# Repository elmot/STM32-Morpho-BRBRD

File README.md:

# STM32-Morpho-BRBRD

Prototyping shield for any STM32 Nucleo64 board.

### Features:

* 55x70 mm
* All MCU pins solderable
* Wide DIL-28 footprint
* Narrow DIL-28 footprint
* (T)SSOP-28 (pitch 0.65mm) footprint (bottom)
* SOP-28 (pitch 1.27mm) footprint (top)
* Four SOT23-5 footprints (two per side)
* Six 1206 footprints in two chains (one chain per side)
* Free pads and pins for custom soldering

### NOTE

Original STM Morpho form-factor contains 2 * 19 connectrors. This shield uses 2 * 20 which are easier to buy. Be careful during soldering and connecting the shield to the Nucleo board.

### Status

12-Aug-18: First batch of PCBs submitted to PCB manufacturer

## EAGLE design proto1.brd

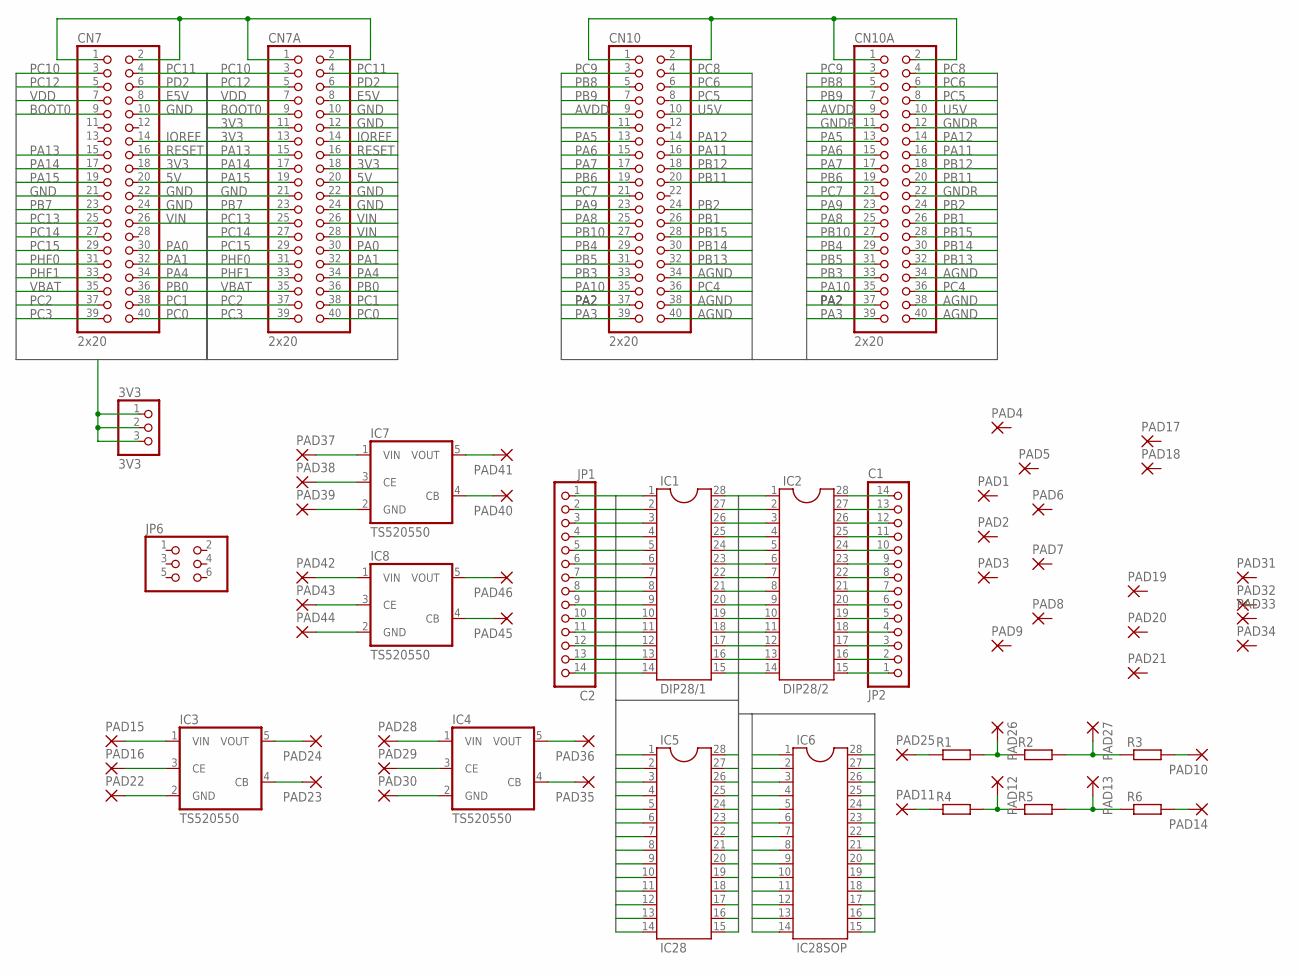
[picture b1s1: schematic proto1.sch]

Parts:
3V3: 3V3; 1X03
CN7, CN7A, CN10, CN10A: 2x20; 2X20
IC1: DIP28/1; DIL28-6
IC2: DIP28/2; DIL28-3
IC3, IC4, IC7, IC8: TS520550; SOT25
IC5: IC28; SSOP28
IC6: IC28SOP; SOP28
JP1: C2; 1X14
JP2: C1; 1X14
JP6: PINHD-2X3; 2X03
PAD1, PAD2, PAD3, PAD4, PAD5, PAD6, PAD7, PAD8, PAD9, PAD10, PAD11, PAD12, PAD13, PAD14, PAD15, PAD16, PAD17, PAD18, PAD19, PAD20, PAD21, PAD22, PAD23, PAD24, PAD25, PAD26, PAD27, PAD28, PAD29, PAD30, PAD31, PAD32, PAD33, PAD34, PAD35, PAD36, PAD37, PAD38, PAD39, PAD40, PAD41, PAD42, PAD43, PAD44, PAD45, PAD46: SMD2; SMD1,27-2,54
R1, R2, R3, R4, R5, R6: R-EU_R1206; R1206

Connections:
3V3: 3V3.1, 3V3.2, 3V3.3, CN7.18, CN7A.11, CN7A.13, CN7A.18
5V: CN7.20, CN7A.20
AGND: CN10.34, CN10.38, CN10.40, CN10A.34, CN10A.38, CN10A.40
AVDD: CN10.9, CN10A.9
BOOT0: CN7.9, CN7A.9
E5V: CN7.8, CN7A.8
GND: CN7.10, CN7.21, CN7.22, CN7.24, CN7A.10, CN7A.12, CN7A.21, CN7A.22, CN7A.24
GNDR: CN10.11, CN10A.11, CN10A.12, CN10A.22
IC1: IC1.1, IC5.1, IC6.28, JP1.1
IC2: IC1.2, IC5.2, IC6.27, JP1.2
IC3: IC1.3, IC5.3, IC6.26, JP1.3
IC4: IC1.4, IC5.4, IC6.25, JP1.4
IC5: IC1.5, IC5.5, IC6.24, JP1.5
IC6: IC1.6, IC5.6, IC6.23, JP1.6
IC7: IC1.7, IC5.7, IC6.22, JP1.7
IC8: IC1.8, IC5.8, IC6.21, JP1.8
IC9: IC1.9, IC5.9, IC6.20, JP1.9
IC10: IC1.10, IC5.10, IC6.19, JP1.10
IC11: IC1.11, IC5.11, IC6.18, JP1.11
IC12: IC1.12, IC5.12, IC6.17, JP1.12
IC13: IC1.13, IC5.13, IC6.16, JP1.13
IC14: IC1.14, IC5.14, IC6.15, JP1.14
IC15: IC1.15, IC2.14, IC5.15, IC6.14
IC16: IC1.16, IC2.13, IC5.16, IC6.13
IC17: IC1.17, IC2.12, IC5.17, IC6.12
IC18: IC1.18, IC2.11, IC5.18, IC6.11
IC19: IC1.19, IC2.10, IC5.19, IC6.10
IC20: IC1.20, IC2.9, IC5.20, IC6.9
IC21: IC1.21, IC2.8, IC5.21, IC6.8
IC22: IC1.22, IC2.7, IC5.22, IC6.7
IC23: IC1.23, IC2.6, IC5.23, IC6.6
IC24: IC1.24, IC2.5, IC5.24, IC6.5
IC25: IC1.25, IC2.4, IC5.25, IC6.4
IC26: IC1.26, IC2.3, IC5.26, IC6.3
IC27: IC1.27, IC2.2, IC5.27, IC6.2
IC28: IC1.28, IC2.1, IC5.28, IC6.1
IOREF: CN7.14, CN7A.14
unnamed: CN10.1, CN10.2, CN10A.1, CN10A.2
unnamed: CN7.1, CN7.2, CN7A.1, CN7A.2
unnamed: IC2.28, JP2.14
unnamed: IC2.27, JP2.13
unnamed: IC2.26, JP2.12
unnamed: IC2.25, JP2.11
unnamed: IC2.24, JP2.10
unnamed: IC2.23, JP2.9
unnamed: IC2.22, JP2.8
unnamed: IC2.21, JP2.7
unnamed: IC2.20, JP2.6
unnamed: IC2.19, JP2.5
unnamed: IC2.18, JP2.4
unnamed: IC2.17, JP2.3
unnamed: IC2.16, JP2.2
unnamed: IC2.15, JP2.1
unnamed: PAD25.1, R1.1
unnamed: PAD26.1, R1.2, R2.1
unnamed: PAD27.1, R2.2, R3.1
unnamed: PAD10.1, R3.2
unnamed: PAD11.1, R4.1
unnamed: PAD12.1, R4.2, R5.1
unnamed: PAD13.1, R5.2, R6.1
unnamed: PAD14.1, R6.2
unnamed: IC3.1 (VIN), PAD15.1
unnamed: IC3.3 (CE), PAD16.1
unnamed: IC3.2 (GND), PAD22.1
unnamed: IC3.4 (CB), PAD23.1
unnamed: IC3.5 (VOUT), PAD24.1
unnamed: IC4.1 (VIN), PAD28.1
unnamed: IC4.3 (CE), PAD29.1
unnamed: IC4.2 (GND), PAD30.1
unnamed: IC4.4 (CB), PAD35.1
unnamed: IC4.5 (VOUT), PAD36.1
unnamed: IC7.1 (VIN), PAD37.1
unnamed: IC7.3 (CE), PAD38.1
unnamed: IC7.2 (GND), PAD39.1
unnamed: IC7.4 (CB), PAD40.1
unnamed: IC7.5 (VOUT), PAD41.1
unnamed: IC8.1 (VIN), PAD42.1
unnamed: IC8.3 (CE), PAD43.1
unnamed: IC8.2 (GND), PAD44.1
unnamed: IC8.4 (CB), PAD45.1
unnamed: IC8.5 (VOUT), PAD46.1
PA0: CN7.30, CN7A.30
PA1: CN7.32, CN7A.32
PA2: CN10.37, CN10A.37
PA3: CN10.39, CN10A.39
PA4: CN7.34, CN7A.34
PA5: CN10.13, CN10A.13
PA6: CN10.15, CN10A.15
PA7: CN10.17, CN10A.17
PA8: CN10.25, CN10A.25
PA9: CN10.23, CN10A.23
PA10: CN10.35, CN10A.35
PA11: CN10.16, CN10A.16
PA12: CN10.14, CN10A.14
PA13: CN7.15, CN7A.15
PA14: CN7.17, CN7A.17
PA15: CN7.19, CN7A.19
PB0: CN7.36, CN7A.36
PB1: CN10.26, CN10A.26
PB2: CN10.24, CN10A.24
PB3: CN10.33, CN10A.33
PB4: CN10.29, CN10A.29
PB5: CN10.31, CN10A.31
PB6: CN10.19, CN10A.19
PB7: CN7.23, CN7A.23
PB8: CN10.5, CN10A.5
PB9: CN10.7, CN10A.7
PB10: CN10.27, CN10A.27
PB11: CN10.20, CN10A.20
PB12: CN10.18, CN10A.18
PB13: CN10.32, CN10A.32
PB14: CN10.30, CN10A.30
PB15: CN10.28, CN10A.28
PC0: CN7.40, CN7A.40
PC1: CN7.38, CN7A.38
PC2: CN7.37, CN7A.37
PC3: CN7.39, CN7A.39
PC4: CN10.36, CN10A.36
PC5: CN10.8, CN10A.8
PC6: CN10.6, CN10A.6
PC7: CN10.21, CN10A.21
PC8: CN10.4, CN10A.4
PC9: CN10.3, CN10A.3
PC10: CN7.3, CN7A.3
PC11: CN7.4, CN7A.4
PC12: CN7.5, CN7A.5
PC13: CN7.25, CN7A.25
PC14: CN7.27, CN7A.27
PC15: CN7.29, CN7A.29
PD2: CN7.6, CN7A.6
PHF0: CN7.31, CN7A.31
PHF1: CN7.33, CN7A.33
RESET: CN7.16, CN7A.16
U5V: CN10.10, CN10A.10
VBAT: CN7.35, CN7A.35
VDD: CN7.7, CN7A.7
VIN: CN7.26, CN7A.26, CN7A.28

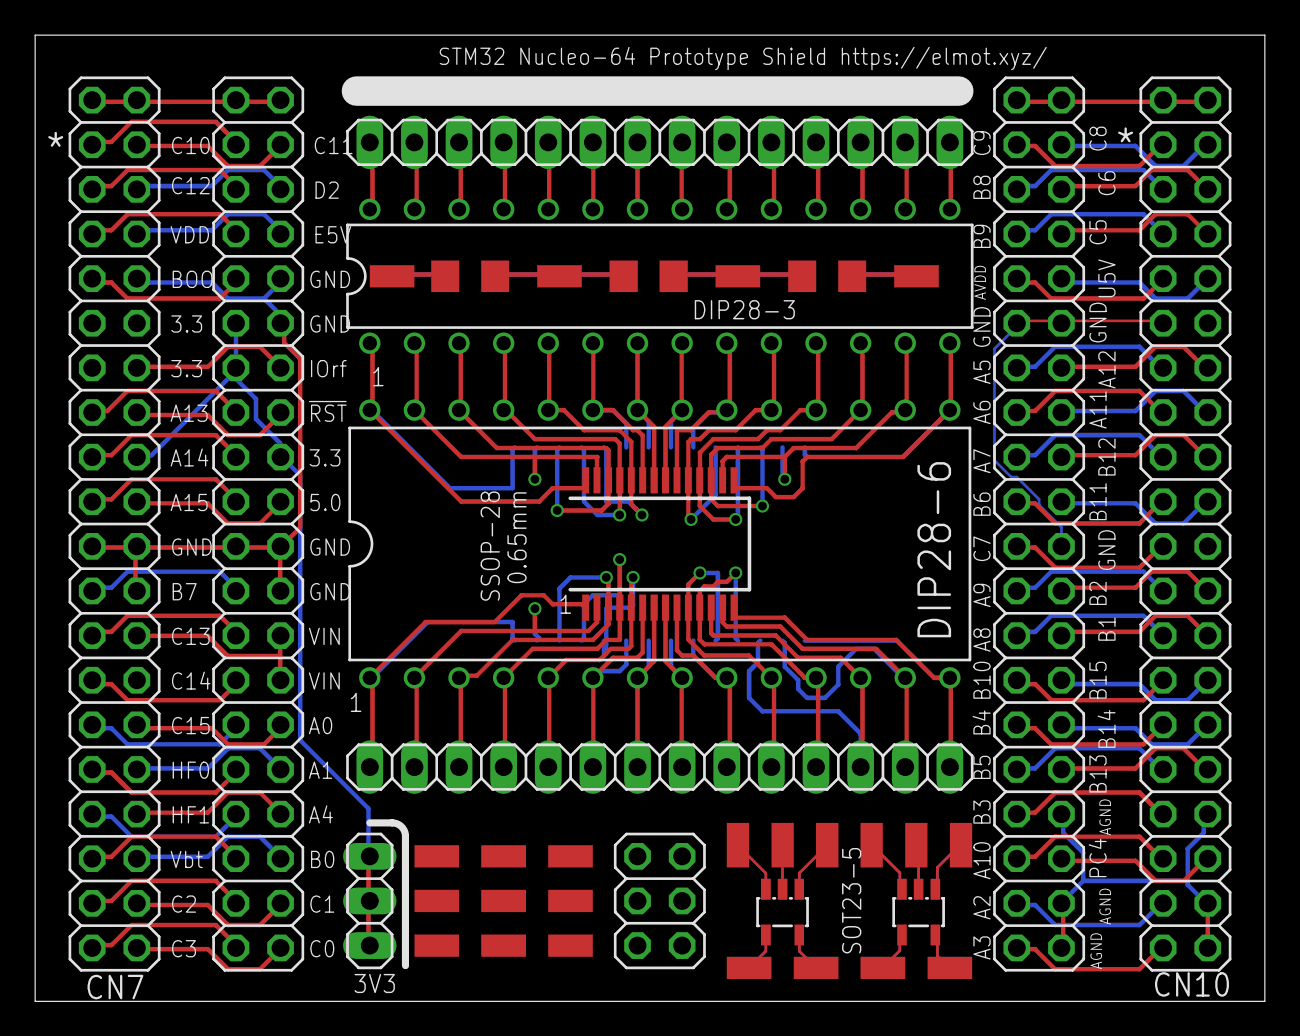
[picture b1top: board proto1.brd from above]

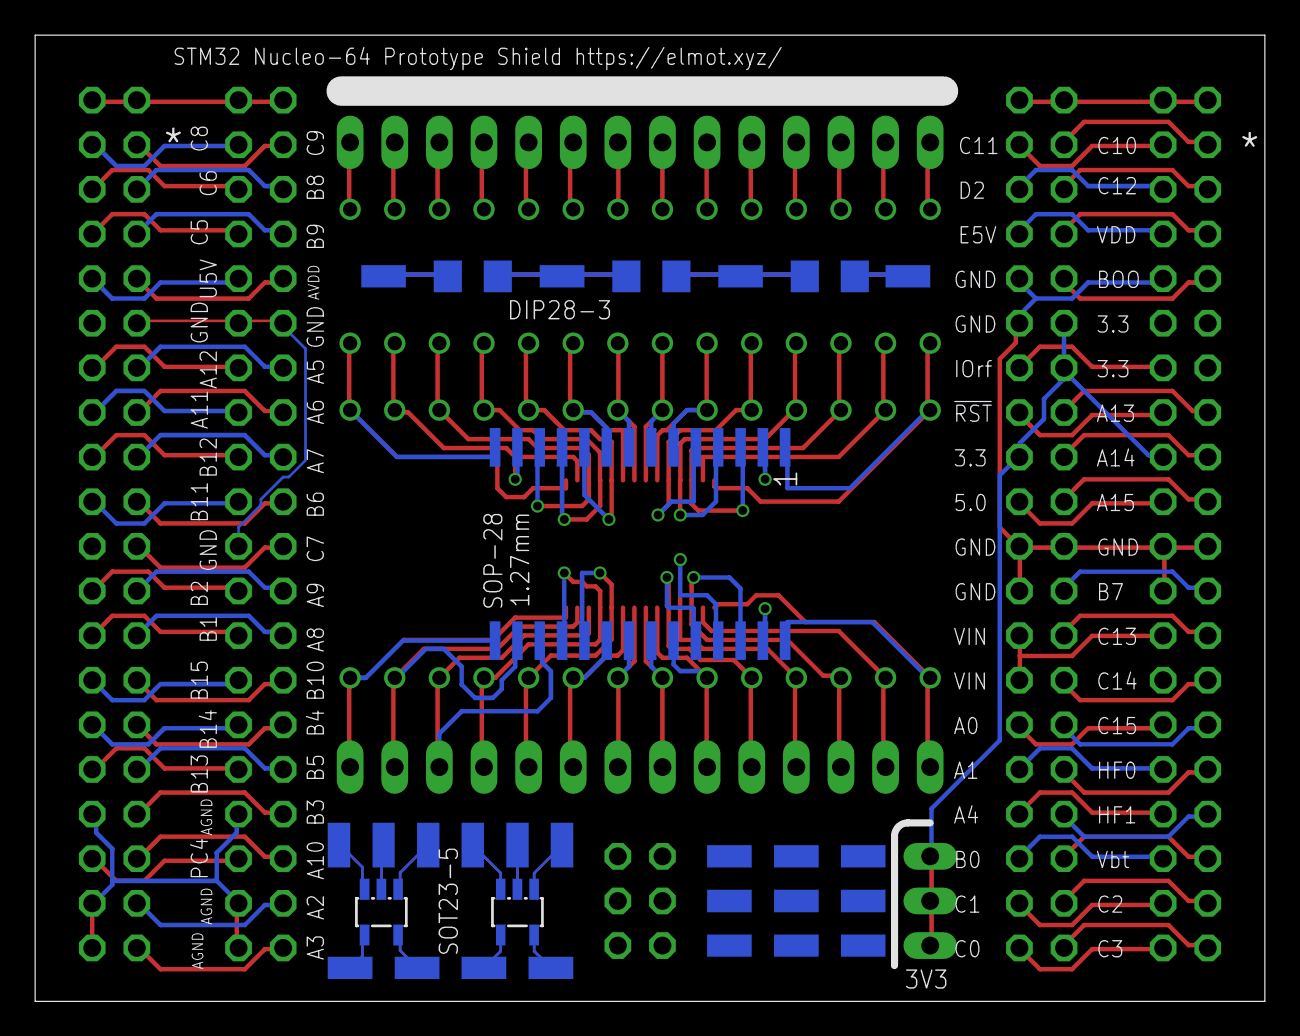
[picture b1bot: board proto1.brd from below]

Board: 2 copper layers, 70.0 x 55.0 mm, 68 parts (29 on the bottom side), 137 nets.

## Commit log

2018-08-12 Board picture added
2018-08-12 Create LICENSE
2018-08-12 Set theme jekyll-theme-hacker
